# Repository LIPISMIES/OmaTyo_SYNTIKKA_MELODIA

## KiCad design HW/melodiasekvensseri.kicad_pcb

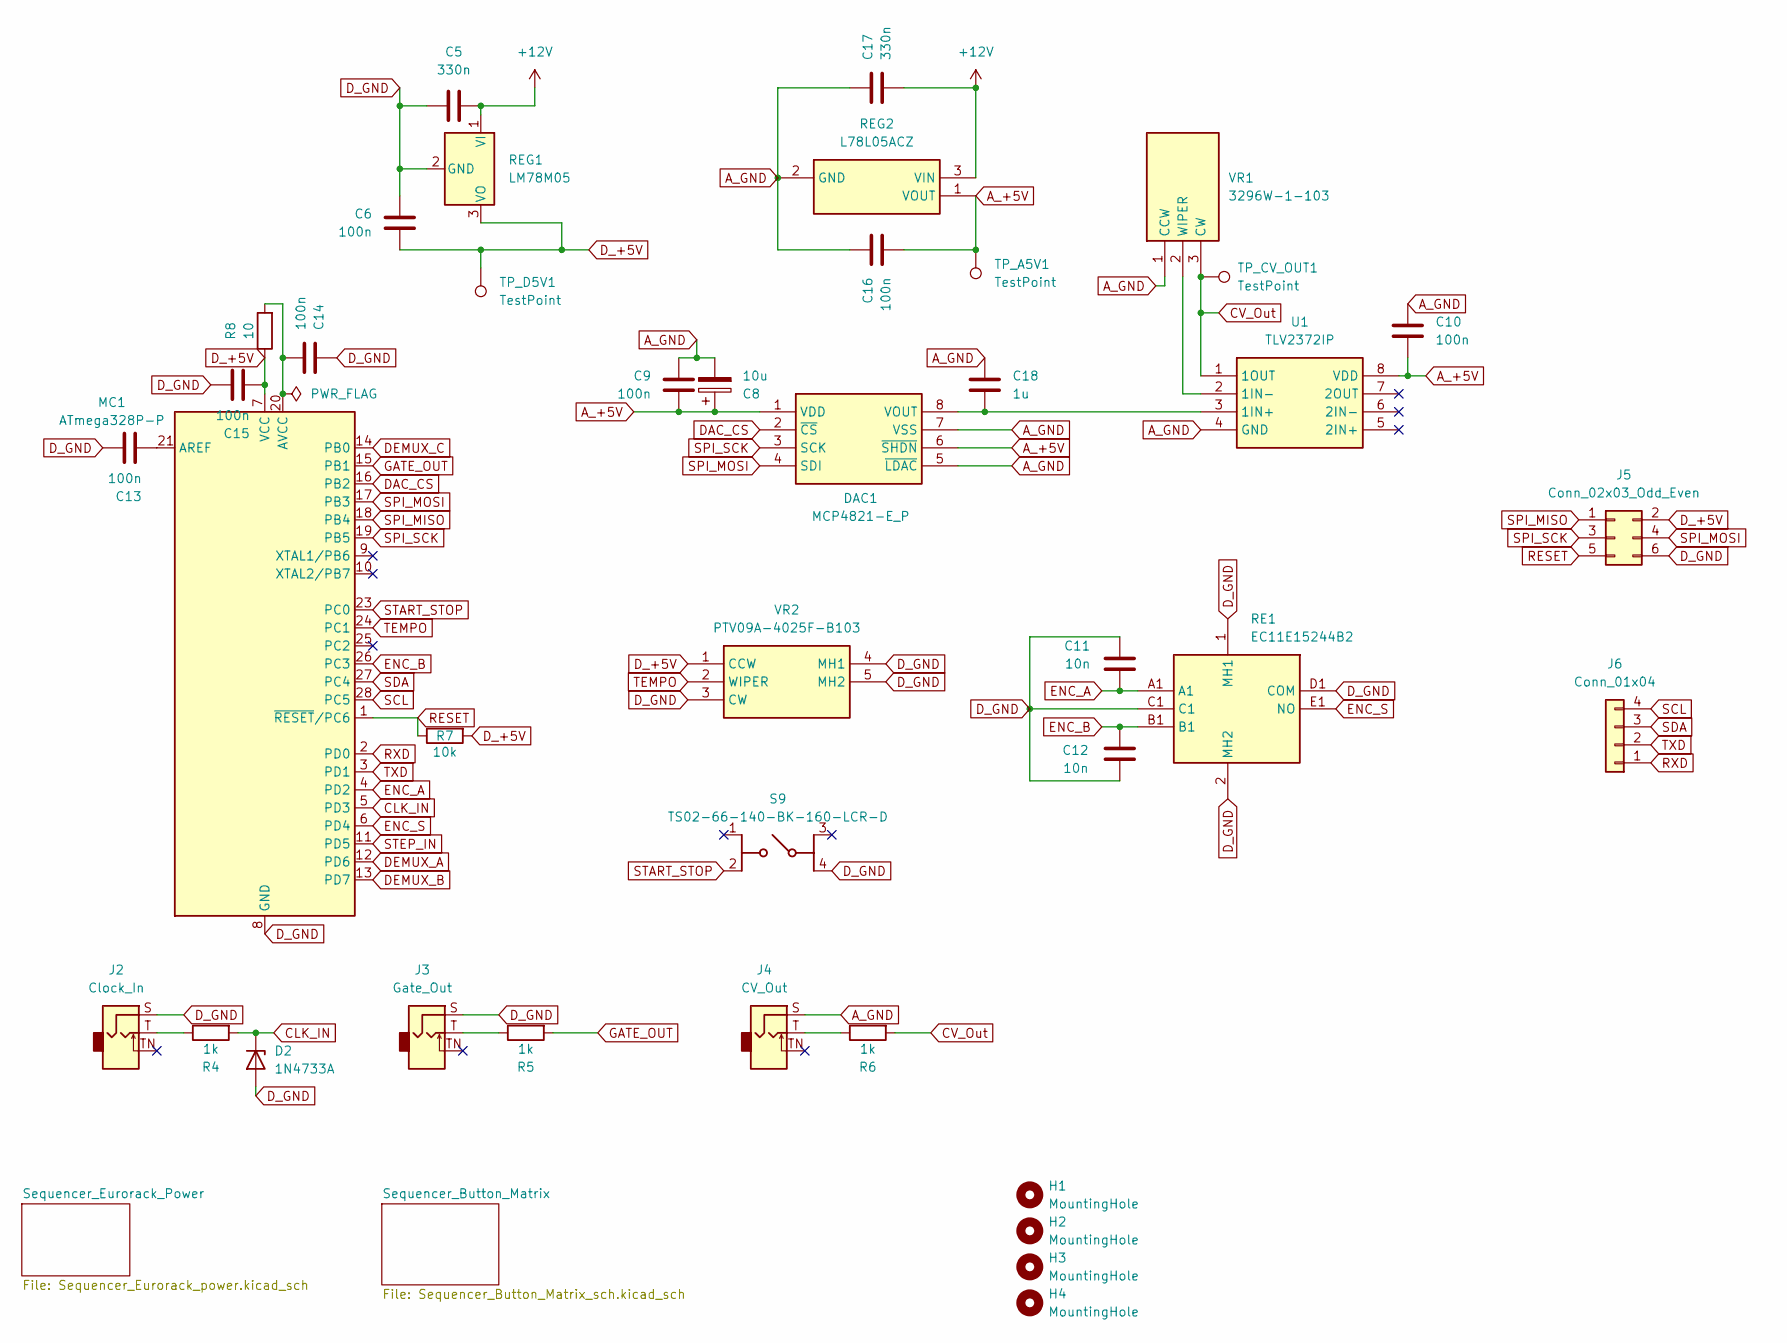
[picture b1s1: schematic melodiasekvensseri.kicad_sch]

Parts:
C5, C17: 330n; C_Disc_D5.0mm_W2.5mm_P5.00mm
C6, C9, C10, C13, C14, C15, C16: 100n; C_Disc_D5.0mm_W2.5mm_P5.00mm
C8: 10u; C_Disc_D5.0mm_W2.5mm_P5.00mm
C11, C12: 10n; C_Disc_D5.0mm_W2.5mm_P5.00mm
C18: 1u; C_Disc_D5.0mm_W2.5mm_P5.00mm
D2: 1N4733A; D_DO-41_SOD81_P10.16mm_Horizontal
DAC1: MCP4821-E_P; DIP794W53P254L959H508Q8N; Mouser Part Number 579-MCP4821-E/P
H1, H2, H3, H4: MountingHole; MountingHole_3.2mm_M3
J2: Clock_In; Adafruit_BBF_3_5mm_Mono_Jack
J3: Gate_Out; Adafruit_BBF_3_5mm_Mono_Jack
J4: CV_Out; Adafruit_BBF_3_5mm_Mono_Jack
J5: Conn_02x03_Odd_Even; PinHeader_2x03_P2.54mm_Vertical
J6: Conn_01x04; PinHeader_1x04_P2.54mm_Vertical
MC1: ATmega328P-P; DIP-28_W7.62mm
R4, R5, R6: 1k; Resistor_SMD+THTuniversal_0805to1206_RM10_HandSoldering_Rev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
R7: 10k; R_Axial_DIN0207_L6.3mm_D2.5mm_P10.16mm_Horizontal
R8: 10; R_Axial_DIN0207_L6.3mm_D2.5mm_P10.16mm_Horizontal
RE1: EC11E15244B2; Mouser Part Number 688-EC11E15244B2
REG1: LM78M05; TO-220-3_Vertical; Mouser Part Number 511-L78L05ACZ
REG2: L78L05ACZ; Mouser Part Number 511-L78L05ACZ
S9: TS02-66-140-BK-160-LCR-D; TS0266100BK100LCRD; Mouser Part Number 179-TS0266140BK160LC
TP_A5V1: TestPoint; TestPoint_THTPad_1.5x1.5mm_Drill0.7mm
TP_CV_OUT1: TestPoint; TestPoint_THTPad_1.5x1.5mm_Drill0.7mm
TP_D5V1: TestPoint; TestPoint_THTPad_1.5x1.5mm_Drill0.7mm
U1: TLV2372IP; DIP794W53P254L959H508Q8N; Mouser Part Number 595-TLV2372IP
VR1: 3296W-1-103; 3296W1103; Mouser Part Number 652-3296W-1-103
VR2: PTV09A-4025F-B103; PTV09A4025FB103; Mouser Part Number 652-PTV09A-4025FB103

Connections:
+12V: C5.2, C17.2, REG1.1 (VI), REG2.3 (VIN); also elsewhere on the board
A_+5V: C8.1, C9.2, C10.2, C16.2, DAC1.1 (VDD), DAC1.6 (~SHDN), REG2.1 (VOUT), TP_A5V1.1 (1_1), U1.8 (VDD)
A_GND: C8.2, C9.1, C10.1, C16.1, C17.1, C18.1, DAC1.5 (~LDAC), DAC1.7 (VSS), J4.S, REG2.2 (GND), U1.4 (GND), VR1.1 (CCW); also elsewhere on the board
CLK_IN: D2.1 (K), MC1.5 (PD3), R4.2
CV_Out: R6.2, TP_CV_OUT1.1 (1_1), U1.1 (1OUT), VR1.3 (CW)
DAC_CS: DAC1.2 (~CS), MC1.16 (PB2)
DEMUX_A: MC1.12 (PD6); also elsewhere on the board
DEMUX_B: MC1.13 (PD7); also elsewhere on the board
DEMUX_C: MC1.14 (PB0); also elsewhere on the board
D_+5V: C6.2, C15.2, J5.2, MC1.7 (VCC), R7.2, R8.1, REG1.3 (VO), TP_D5V1.1 (1_1), VR2.1 (CCW); also elsewhere on the board
D_GND: C5.1, C6.1, C11.1, C12.2, C13.1, C14.1, C15.1, D2.2 (A), J2.S, J3.S, J5.6, MC1.8 (GND), MC1.22 (GND), RE1.1 (MH1), RE1.2 (MH2), RE1.C1, RE1.D1 (COM), REG1.2 (GND), S9.4 (COM_2), VR2.3 (CW), VR2.4 (MH1), VR2.5 (MH2); also elsewhere on the board
ENC_A: C11.2, MC1.4 (PD2), RE1.A1
ENC_B: C12.1, MC1.26 (PC3), RE1.B1
ENC_S: MC1.6 (PD4), RE1.E1 (NO)
GATE_OUT: MC1.15 (PB1), R5.2
unnamed: C18.2, DAC1.8 (VOUT), U1.3 (1IN+)
unnamed: J2.T, R4.1
unnamed: J3.T, R5.1
unnamed: J4.T, R6.1
unnamed: C13.2, MC1.21 (AREF)
unnamed: C14.2, MC1.20 (AVCC), R8.2
unnamed: U1.2 (1IN-), VR1.2 (WIPER)
RESET: J5.5, MC1.1 (~RESET/PC6), R7.1
RXD: J6.1, MC1.2 (PD0)
SCL: J6.4, MC1.28 (PC5)
SDA: J6.3, MC1.27 (PC4)
SPI_MISO: J5.1, MC1.18 (PB4)
SPI_MOSI: DAC1.4 (SDI), J5.4, MC1.17 (PB3)
SPI_SCK: DAC1.3 (SCK), J5.3, MC1.19 (PB5)
START_STOP: MC1.23 (PC0), S9.2 (NO_2)
STEP_IN: MC1.11 (PD5); also elsewhere on the board
TEMPO: MC1.24 (PC1), VR2.2 (WIPER)
TXD: J6.2, MC1.3 (PD1)

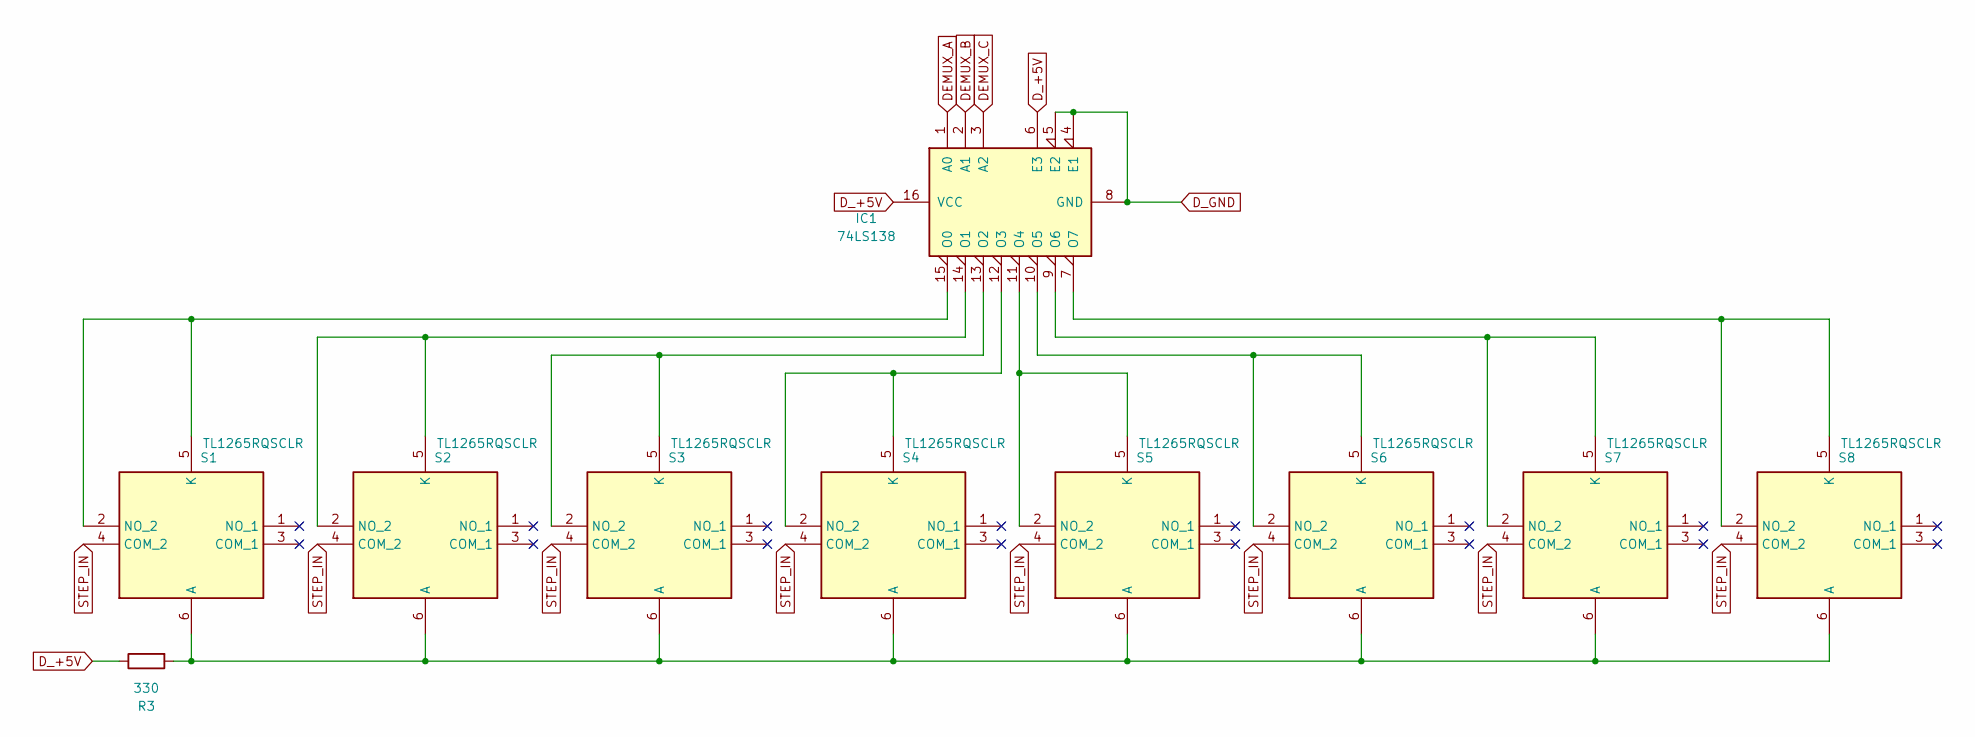
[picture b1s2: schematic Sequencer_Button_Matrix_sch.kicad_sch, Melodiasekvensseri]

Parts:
IC1: 74LS138; DIP-16_W7.62mm
R3: 330; R_Axial_DIN0207_L6.3mm_D2.5mm_P10.16mm_Horizontal
S1, S2, S3, S4, S5, S6, S7, S8: TL1265RQSCLR; Mouser Part Number 612-TL1265RQSCLR

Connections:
DEMUX_A: IC1.1 (A0); also elsewhere on the board
DEMUX_B: IC1.2 (A1); also elsewhere on the board
DEMUX_C: IC1.3 (A2); also elsewhere on the board
D_+5V: IC1.6 (E3), IC1.16 (VCC), R3.1; also elsewhere on the board
D_GND: IC1.4 (E1), IC1.5 (E2), IC1.8 (GND); also elsewhere on the board
unnamed: IC1.15 (O0), S1.2 (NO_2), S1.5 (K)
unnamed: IC1.14 (O1), S2.2 (NO_2), S2.5 (K)
unnamed: IC1.13 (O2), S3.2 (NO_2), S3.5 (K)
unnamed: IC1.12 (O3), S4.2 (NO_2), S4.5 (K)
unnamed: IC1.11 (O4), S5.2 (NO_2), S5.5 (K)
unnamed: IC1.10 (O5), S6.2 (NO_2), S6.5 (K)
unnamed: IC1.9 (O6), S7.2 (NO_2), S7.5 (K)
unnamed: IC1.7 (O7), S8.2 (NO_2), S8.5 (K)
unnamed: R3.2, S1.6 (A), S2.6 (A), S3.6 (A), S4.6 (A), S5.6 (A), S6.6 (A), S7.6 (A), S8.6 (A)
STEP_IN: S1.4 (COM_2), S2.4 (COM_2), S3.4 (COM_2), S4.4 (COM_2), S5.4 (COM_2), S6.4 (COM_2), S7.4 (COM_2), S8.4 (COM_2); also elsewhere on the board

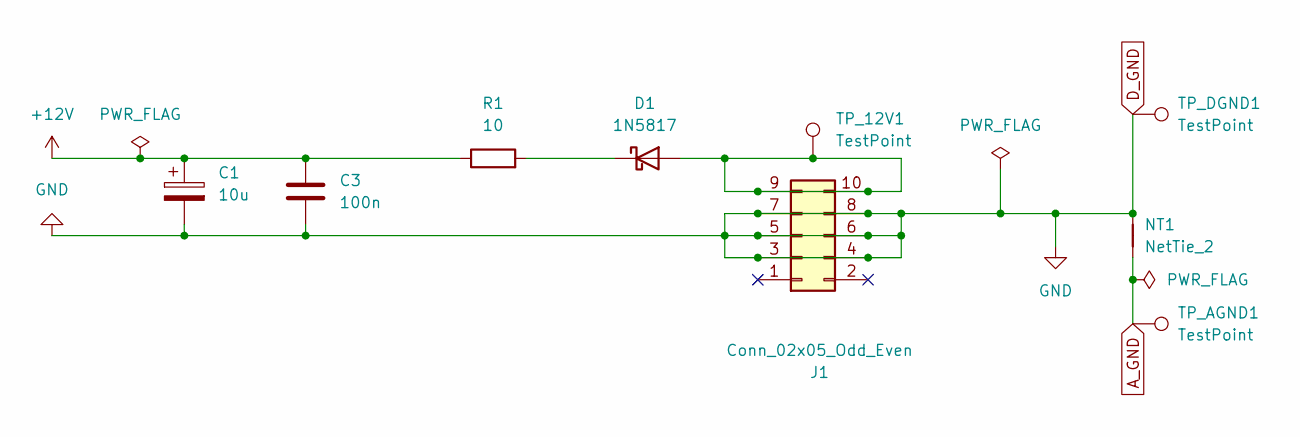
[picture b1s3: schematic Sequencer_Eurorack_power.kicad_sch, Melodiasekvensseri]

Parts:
C1: 10u; CP_Radial_D5.0mm_P2.00mm
C3: 100n; C_Disc_D5.0mm_W2.5mm_P5.00mm
D1: 1N5817; D_DO-41_SOD81_P10.16mm_Horizontal
J1: Conn_02x05_Odd_Even; IDC-Header_2x05_P2.54mm_Vertical
NT1: NetTie_2; NetTie-2_SMD_Pad2.0mm
R1: 10; Resistor_SMD+THTuniversal_0805to1206_RM10_HandSoldering_Rev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
TP_12V1: TestPoint; TestPoint_THTPad_1.5x1.5mm_Drill0.7mm
TP_AGND1: TestPoint; TestPoint_THTPad_1.5x1.5mm_Drill0.7mm
TP_DGND1: TestPoint; TestPoint_THTPad_1.5x1.5mm_Drill0.7mm

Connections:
+12V: C1.1, C3.1, R1.1; also elsewhere on the board
A_GND: NT1.1, TP_AGND1.1 (1_1); also elsewhere on the board
D_GND: C1.2, C3.2, J1.3, J1.4, J1.5, J1.6, J1.7, J1.8, NT1.2, TP_DGND1.1 (1_1); also elsewhere on the board
unnamed: D1.2 (A), J1.9, J1.10, TP_12V1.1 (1_1)
unnamed: D1.1 (K), R1.2

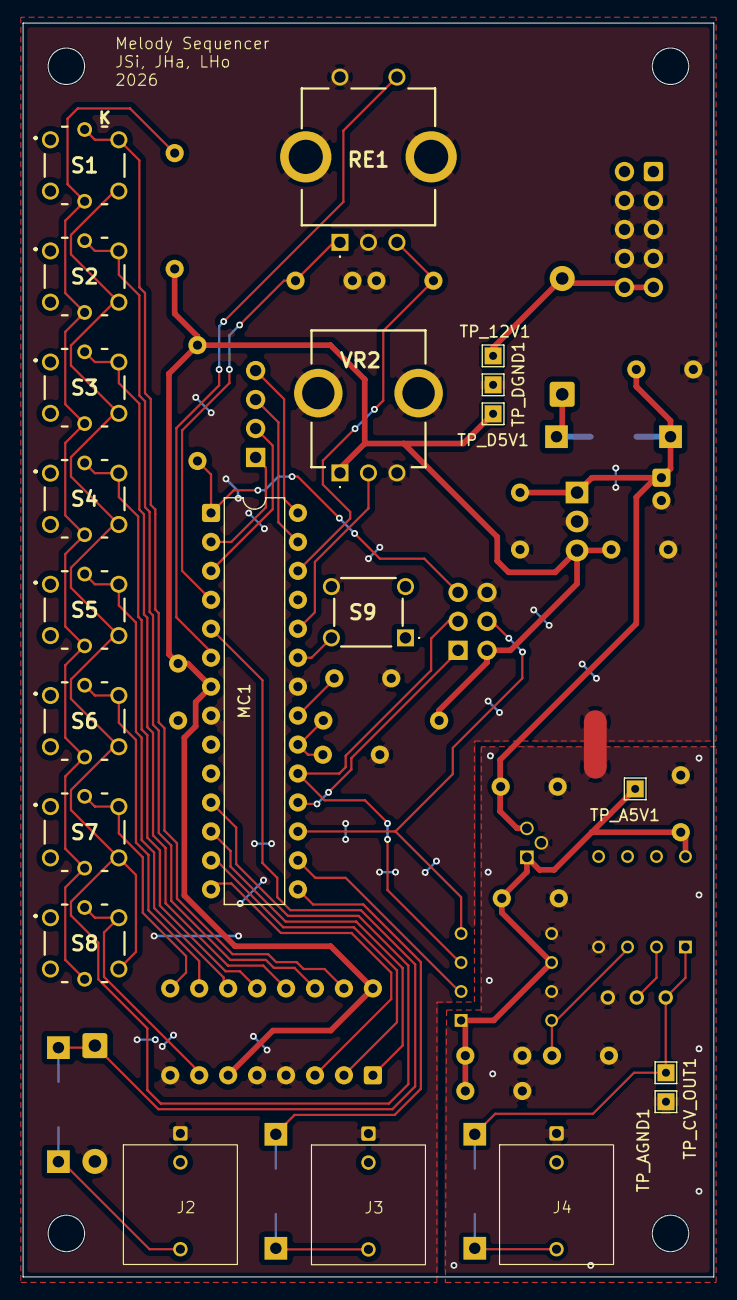
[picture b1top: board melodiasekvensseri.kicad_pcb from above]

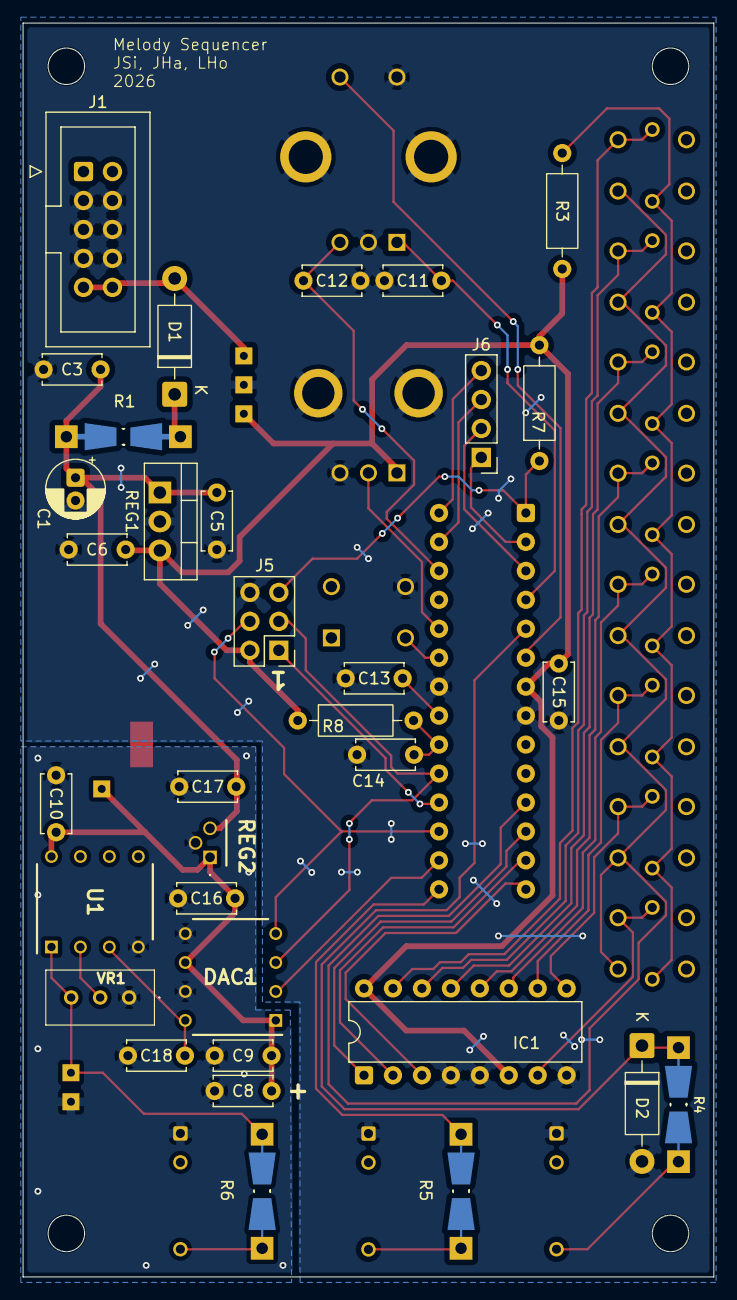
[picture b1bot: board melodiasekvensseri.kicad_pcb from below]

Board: 2 copper layers, 60.6 x 110.0 mm, 59 parts (33 on the bottom side), 44 nets.

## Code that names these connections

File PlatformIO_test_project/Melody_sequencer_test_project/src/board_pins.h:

#pragma once
#include <Arduino.h>

/*

Physical DIP pin   Pin function                     Code pin        Device function

1                  PC6 (PCINT14/RESET)              -               RESET
2                  PD0 (PCINT16/RXD)                0               RXD
3                  PD1 (PCINT17/TXD)                1               TXD
4                  PD2 (PCINT18/INT0)               2               ENC_A
5                  PD3 (PCINT19/OC2B/INT1)          3               CLK_IN
6                  PD4 (PCINT20/XCK/T0)             4               ENC_S
7                  VCC                              -
8                  GND                              -
9                  PB6 (PCINT6/XTAL1/TOSC1)         -               -
10                 PB7 (PCINT7/XTAL2/TOSC2)         -               -
11                 PD5 (PCINT21/OC0B/T1)            5               STEP_IN
12                 PD6 (PCINT22/OC0A/AIN0)          6               DEMUX_A
13                 PD7 (PCINT23/AIN1)               7               DEMUX_B
14                 PB0 (PCINT0/CLKO/ICP1)           8               DEMUX_C
15                 PB1 (OC1A/PCINT1)                9               GATE_OUT
16                 PB2 (SS/OC1B/PCINT2)             10              DAC_CS
17                 PB3 (MOSI/OC2A/PCINT3)           11              SPI_MOSI
18                 PB4 (MISO/PCINT4)                12              SPI_MISO
19                 PB5 (SCK/PCINT5)                 13              SPI_SCK
20                 AVCC                             -
21                 AREF                             -
22                 GND                              -
23                 PC0 (ADC0/PCINT8)                A0              START_STOP
24                 PC1 (ADC1/PCINT9)                A1              TEMPO
25                 PC2 (ADC2/PCINT10)               A2              -
26                 PC3 (ADC3/PCINT11)               A3              ENC_B
27                 PC4 (ADC4/SDA/PCINT12)           A4              SDA
28                 PC5 (ADC5/SCL/PCINT13)           A5              SCL

*/

namespace BoardPins {
    // ========================================================
    // Digital Demux Control Bus & System IO
    // ========================================================
    constexpr uint8_t DEMUX_A = 6;
    constexpr uint8_t DEMUX_B = 7;
    constexpr uint8_t DEMUX_C = 8;

    constexpr uint8_t CLOCK_IN = 3;
    constexpr uint8_t STEP_IN = 5;

    // ========================================================
    // Rotary Encoder Inputs
    // ========================================================
    constexpr uint8_t ENCODER_A = 2;
    constexpr uint8_t ENCODER_SWITCH = 4;
    constexpr uint8_t ENCODER_B = A2;

    // ========================================================
    // Controls & Gate Pulse Input
    // ========================================================
    constexpr uint8_t START_STOP = A0;
    constexpr uint8_t TEMPO = A1;
    constexpr uint8_t GATE_OUT = 9;


    // ========================================================
    // Hardware SPI Interface
    // ========================================================
    constexpr uint8_t DAC_CS = 10;
    constexpr uint8_t DAC_MOSI = 11;
    constexpr uint8_t DAC_SCK = 13;
}
